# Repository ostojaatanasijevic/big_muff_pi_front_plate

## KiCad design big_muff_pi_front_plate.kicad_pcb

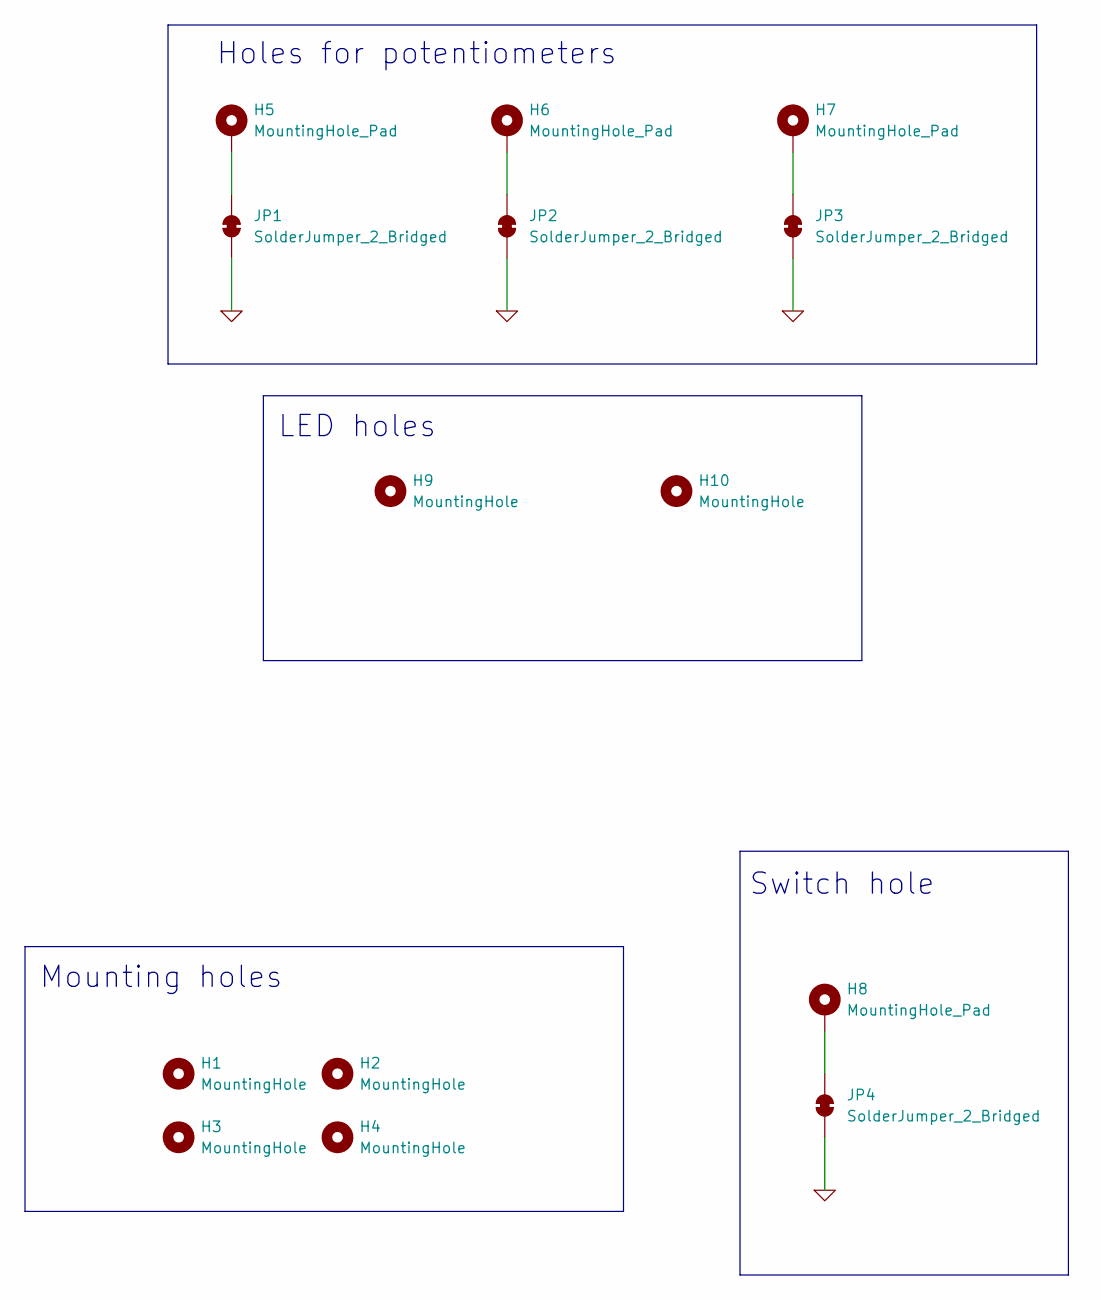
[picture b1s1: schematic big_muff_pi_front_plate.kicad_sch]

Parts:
H1, H2, H3, H4: MountingHole; MountingHole_3.2mm_M3_DIN965_Pad_TopBottom
H5, H6, H7: MountingHole_Pad; plated_pot_hole
H8: MountingHole_Pad; plated_switch_hole
H9, H10: MountingHole; MountingHole_3mm
JP1, JP2, JP3, JP4: SolderJumper_2_Bridged; SolderJumper-2_P1.3mm_Bridged_RoundedPad1.0x1.5mm

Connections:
0: JP1.1 (A), JP2.1 (A), JP3.1 (A), JP4.1 (A)
unnamed: H5.1, JP1.2 (B)
unnamed: H6.1, JP2.2 (B)
unnamed: H7.1, JP3.2 (B)
unnamed: H8.1, JP4.2 (B)

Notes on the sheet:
Mounting holes
Switch hole
LED holes
Holes for potentiometers

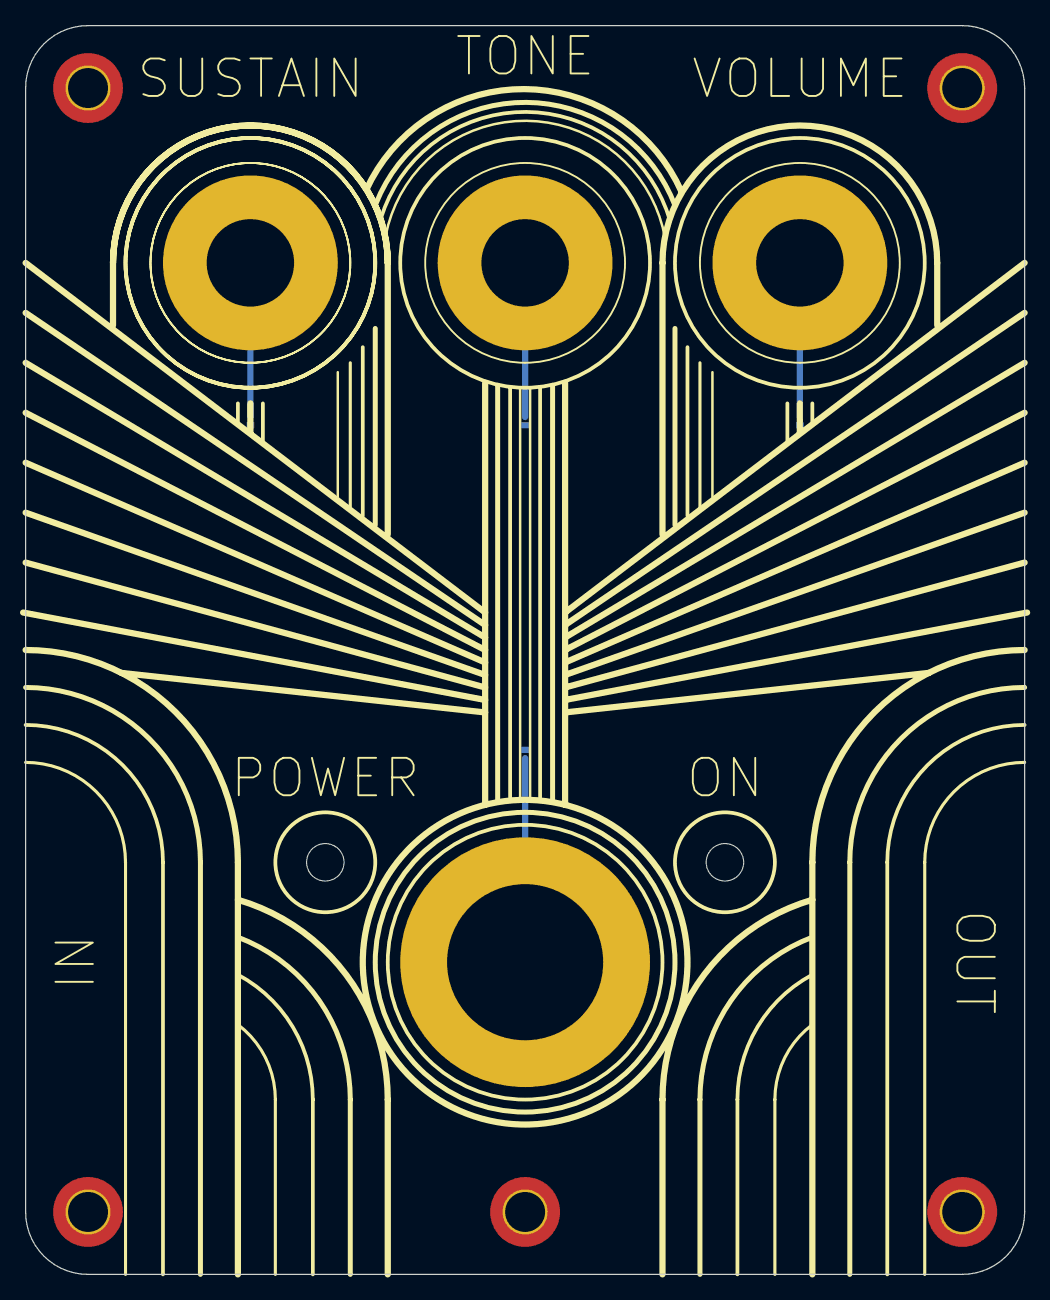
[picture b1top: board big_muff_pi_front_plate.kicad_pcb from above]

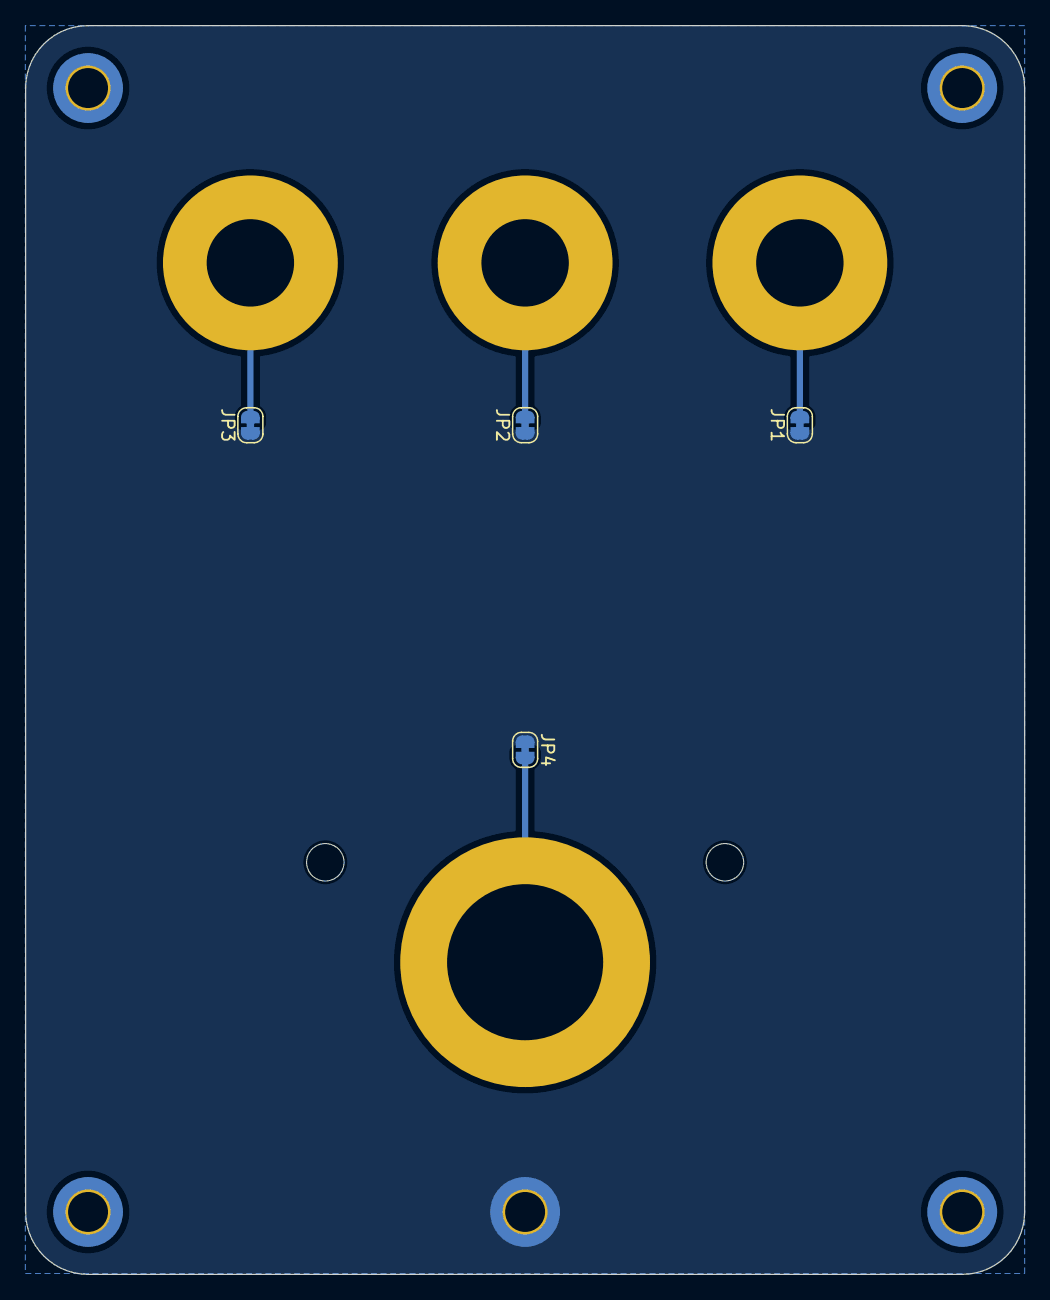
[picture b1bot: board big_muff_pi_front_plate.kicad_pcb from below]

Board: 2 copper layers, 80.0 x 100.0 mm, 15 parts (4 on the bottom side), 5 nets.

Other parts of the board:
H11: MountingHole; MountingHole_3.2mm_M3_DIN965_Pad_TopBottom

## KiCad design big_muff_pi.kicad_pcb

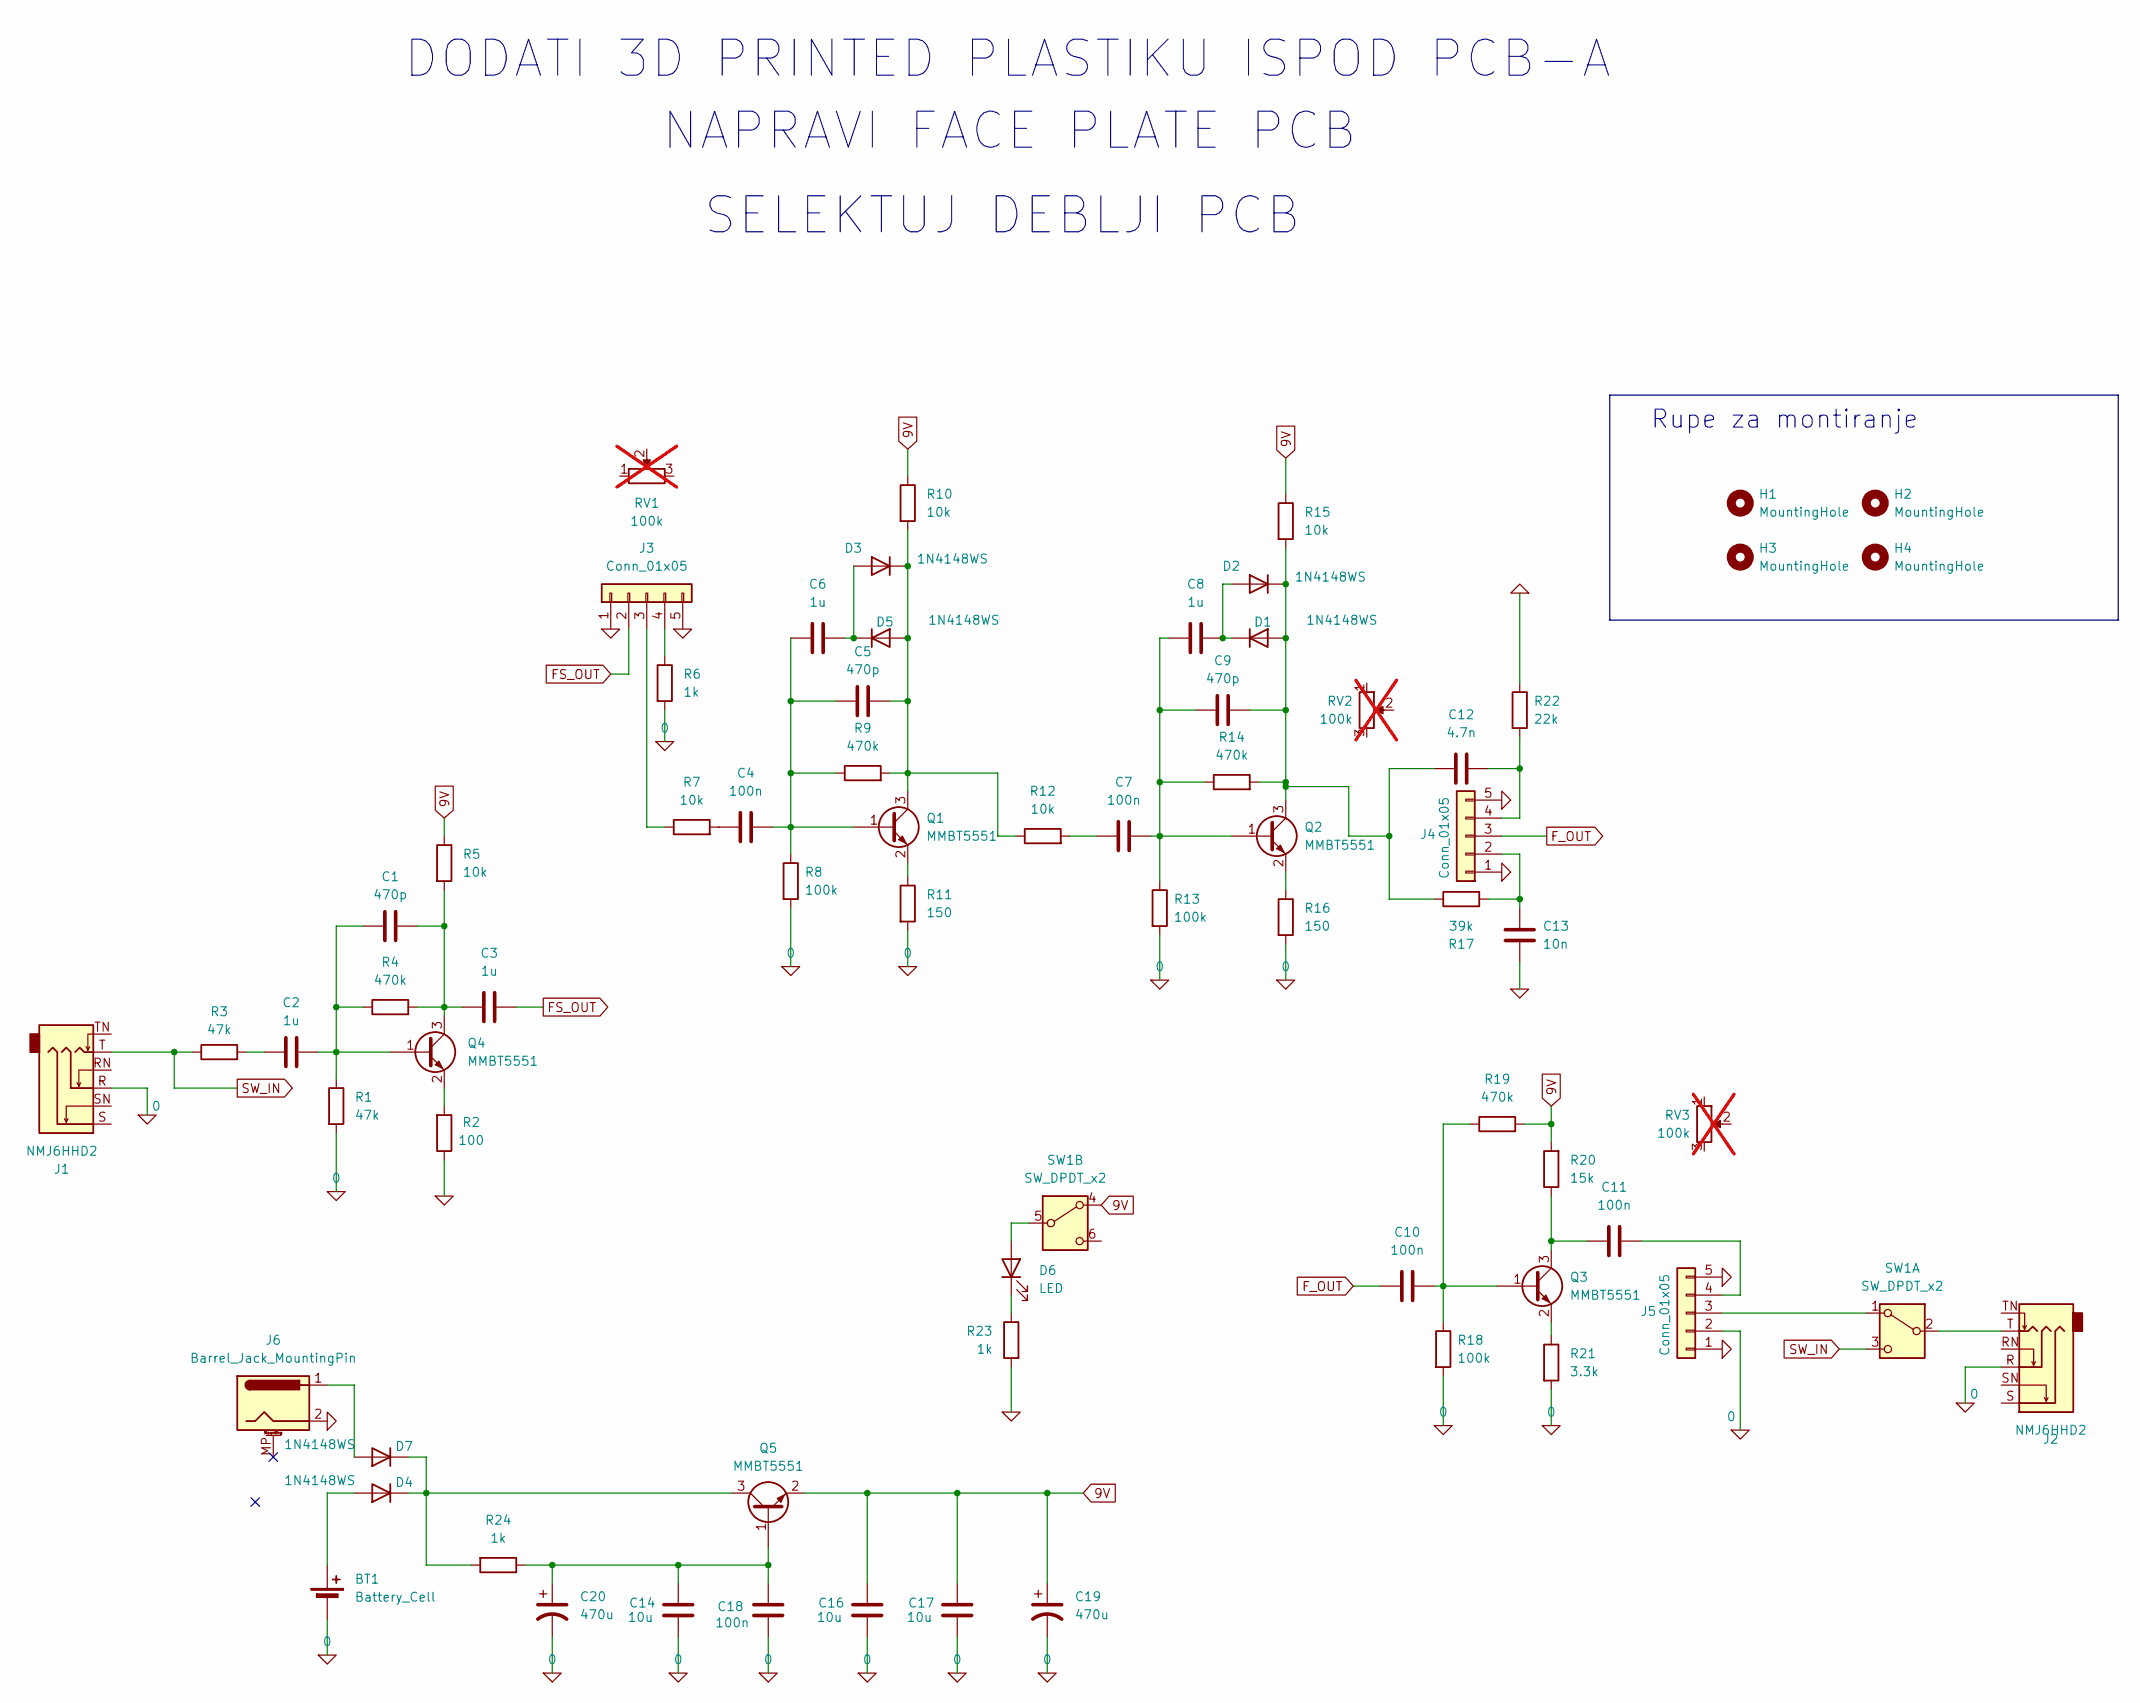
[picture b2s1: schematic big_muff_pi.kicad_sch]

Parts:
BT1: Battery_Cell; BatteryHolder_Eagle_12BH611-GR
C1, C5, C9: 470p; C_0603_1608Metric_Pad1.08x0.95mm_HandSolder; LCSC C1620
C2, C3, C6, C8: 1u; C_0603_1608Metric_Pad1.08x0.95mm_HandSolder; LCSC C15849
C4, C7, C10, C11, C18: 100n; C_0603_1608Metric_Pad1.08x0.95mm_HandSolder; LCSC C14663
C12: 4.7n; C_0603_1608Metric_Pad1.08x0.95mm_HandSolder; LCSC C53987
C13: 10n; C_0603_1608Metric_Pad1.08x0.95mm_HandSolder; LCSC C57112
C14, C16, C17: 10u; C_0603_1608Metric_Pad1.08x0.95mm_HandSolder; LCSC C96446
C19, C20: 470u; CP_Radial_D8.0mm_P3.50mm
D1, D2, D3, D4, D5, D7: 1N4148WS; D_SOD-323; LCSC C2128
D6: LED; LED_D5.0mm
H1, H2, H3, H4: MountingHole; M3_hole_with_spacer
J1, J2: NMJ6HHD2; Jack_6.35mm_Neutrik_NMJ6HHD2_Horizontal
J3, J4, J5: Conn_01x05; JST_EH_B5B-EH-A_1x05_P2.50mm_Vertical
J6: Barrel_Jack_MountingPin; BarrelJack_GCT_DCJ200-10-A_Horizontal
Q1, Q2, Q3, Q4, Q5: MMBT5551; SOT-23; LCSC C2145
R1, R3: 47k; R_0603_1608Metric_Pad0.98x0.95mm_HandSolder; LCSC C25819
R2: 100; R_0603_1608Metric_Pad0.98x0.95mm_HandSolder; LCSC C22775
R4, R9, R14, R19: 470k; R_0603_1608Metric_Pad0.98x0.95mm_HandSolder; LCSC C23178
R5, R7, R10, R12, R15: 10k; R_0603_1608Metric_Pad0.98x0.95mm_HandSolder; LCSC C25804
R6, R23, R24: 1k; R_0603_1608Metric_Pad0.98x0.95mm_HandSolder; LCSC C21190
R8, R13, R18: 100k; R_0603_1608Metric_Pad0.98x0.95mm_HandSolder; LCSC C25803
R11, R16: 150; R_0603_1608Metric_Pad0.98x0.95mm_HandSolder; LCSC C22808
R17: 39k; R_0603_1608Metric_Pad0.98x0.95mm_HandSolder; LCSC C23153
R20: 15k; R_0603_1608Metric_Pad0.98x0.95mm_HandSolder; LCSC C22809
R21: 3.3k; R_0603_1608Metric_Pad0.98x0.95mm_HandSolder; LCSC C22978
R22: 22k; R_0603_1608Metric_Pad0.98x0.95mm_HandSolder; LCSC C31850
RV1, RV2, RV3: 100k; Potentiometer_Alpha_RD901F-40-00D_Single_Vertical; not fitted
SW1: SW_DPDT_x2; switch_DPDT

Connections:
0: BT1.2 (-), C13.1, C14.2, C16.2, C17.2, C18.1, C19.2, C20.2, J1.R, J2.R, J3.1, J3.5, J4.1, J4.5, J5.1, J5.2, J5.5, J6.2, R1.2, R2.1, R6.2, R8.2, R11.2, R13.2, R16.2, R18.2, R21.2, R22.1, R23.2
9V: C16.1, C17.1, C19.1, Q5.2 (E), R5.1, R10.1, R15.1, R19.2, R20.2, SW1.4 (A)
FS_OUT: C3.2, J3.2
F_OUT: C10.1, J4.3
unnamed: BT1.1 (+), D4.2 (A)
unnamed: C2.1, R3.2
unnamed: C4.1, R7.2
unnamed: C7.1, R12.2
unnamed: C9.2, C12.1, D1.2 (A), D2.1 (K), Q2.3 (C), R14.2, R15.2, R17.1
unnamed: C8.2, D1.1 (K), D2.2 (A)
unnamed: C6.2, D3.2 (A), D5.1 (K)
unnamed: C5.2, D3.1 (K), D5.2 (A), Q1.3 (C), R9.2, R10.2, R12.1
unnamed: D4.1 (K), D7.1 (K), Q5.3 (C), R24.2
unnamed: D6.2 (A), SW1.5 (B)
unnamed: D6.1 (K), R23.1
unnamed: D7.2 (A), J6.1
unnamed: J3.3, R7.1
unnamed: J3.4, R6.1
unnamed: C13.2, J4.2, R17.2
unnamed: C12.2, J4.4, R22.2
unnamed: J5.3, SW1.1 (A)
unnamed: C11.2, J5.4
unnamed: C4.2, C5.1, C6.1, Q1.1 (B), R8.1, R9.1
unnamed: Q1.2 (E), R11.1
unnamed: C7.2, C8.1, C9.1, Q2.1 (B), R13.1, R14.1
unnamed: Q2.2 (E), R16.1
unnamed: C10.2, Q3.1 (B), R18.1, R19.1
unnamed: C11.1, Q3.3 (C), R20.1
unnamed: Q3.2 (E), R21.1
unnamed: C1.1, C2.2, Q4.1 (B), R1.1, R4.1
unnamed: C1.2, C3.1, Q4.3 (C), R4.2, R5.2
unnamed: Q4.2 (E), R2.2
unnamed: C14.1, C18.2, C20.1, Q5.1 (B), R24.1
unnamed: J2.T, SW1.2 (B)
SW_IN: J1.T, R3.1, SW1.3 (C)

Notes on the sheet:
DODATI 3D PRINTED PLASTIKU ISPOD PCB-A
NAPRAVI FACE PLATE PCB
Rupe za montiranje
SELEKTUJ DEBLJI PCB

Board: 2 copper layers, 67 parts (0 on the bottom side), 35 nets, no tracks yet.

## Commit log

2023-07-03 Praktično gotova pedala
2025-03-30 Moved to 0603, all basic parts. Placement done.
2025-03-31 Added capacitance, switches.
2025-04-01 Added connectors and switched.
2025-04-01 3D bodies
2025-04-01 Init.
2025-04-01 Back to black.
2025-04-01 Finalized estetics.
2025-04-01 Added input labels.
